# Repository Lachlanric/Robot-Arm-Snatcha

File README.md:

# "Snatcha"

4-DoF Robotic Arm (excluding end effector) + Claw Gripper.

Entire robot (minus electronics) can be laser cut from 3mm wood or acrylic and fastened with M3 screws.

Can be controlled over UART communication (requires USB to UART converter) using either:
1. IK pose control python app `Operation/IK Control/app.py`
   
   OR
2. Oculus Quest 2 controller unity app `Operation/VR Control/Unity`

https://github.com/user-attachments/assets/1d7107a9-4986-4063-b4a9-3a9e8fb0a1fe

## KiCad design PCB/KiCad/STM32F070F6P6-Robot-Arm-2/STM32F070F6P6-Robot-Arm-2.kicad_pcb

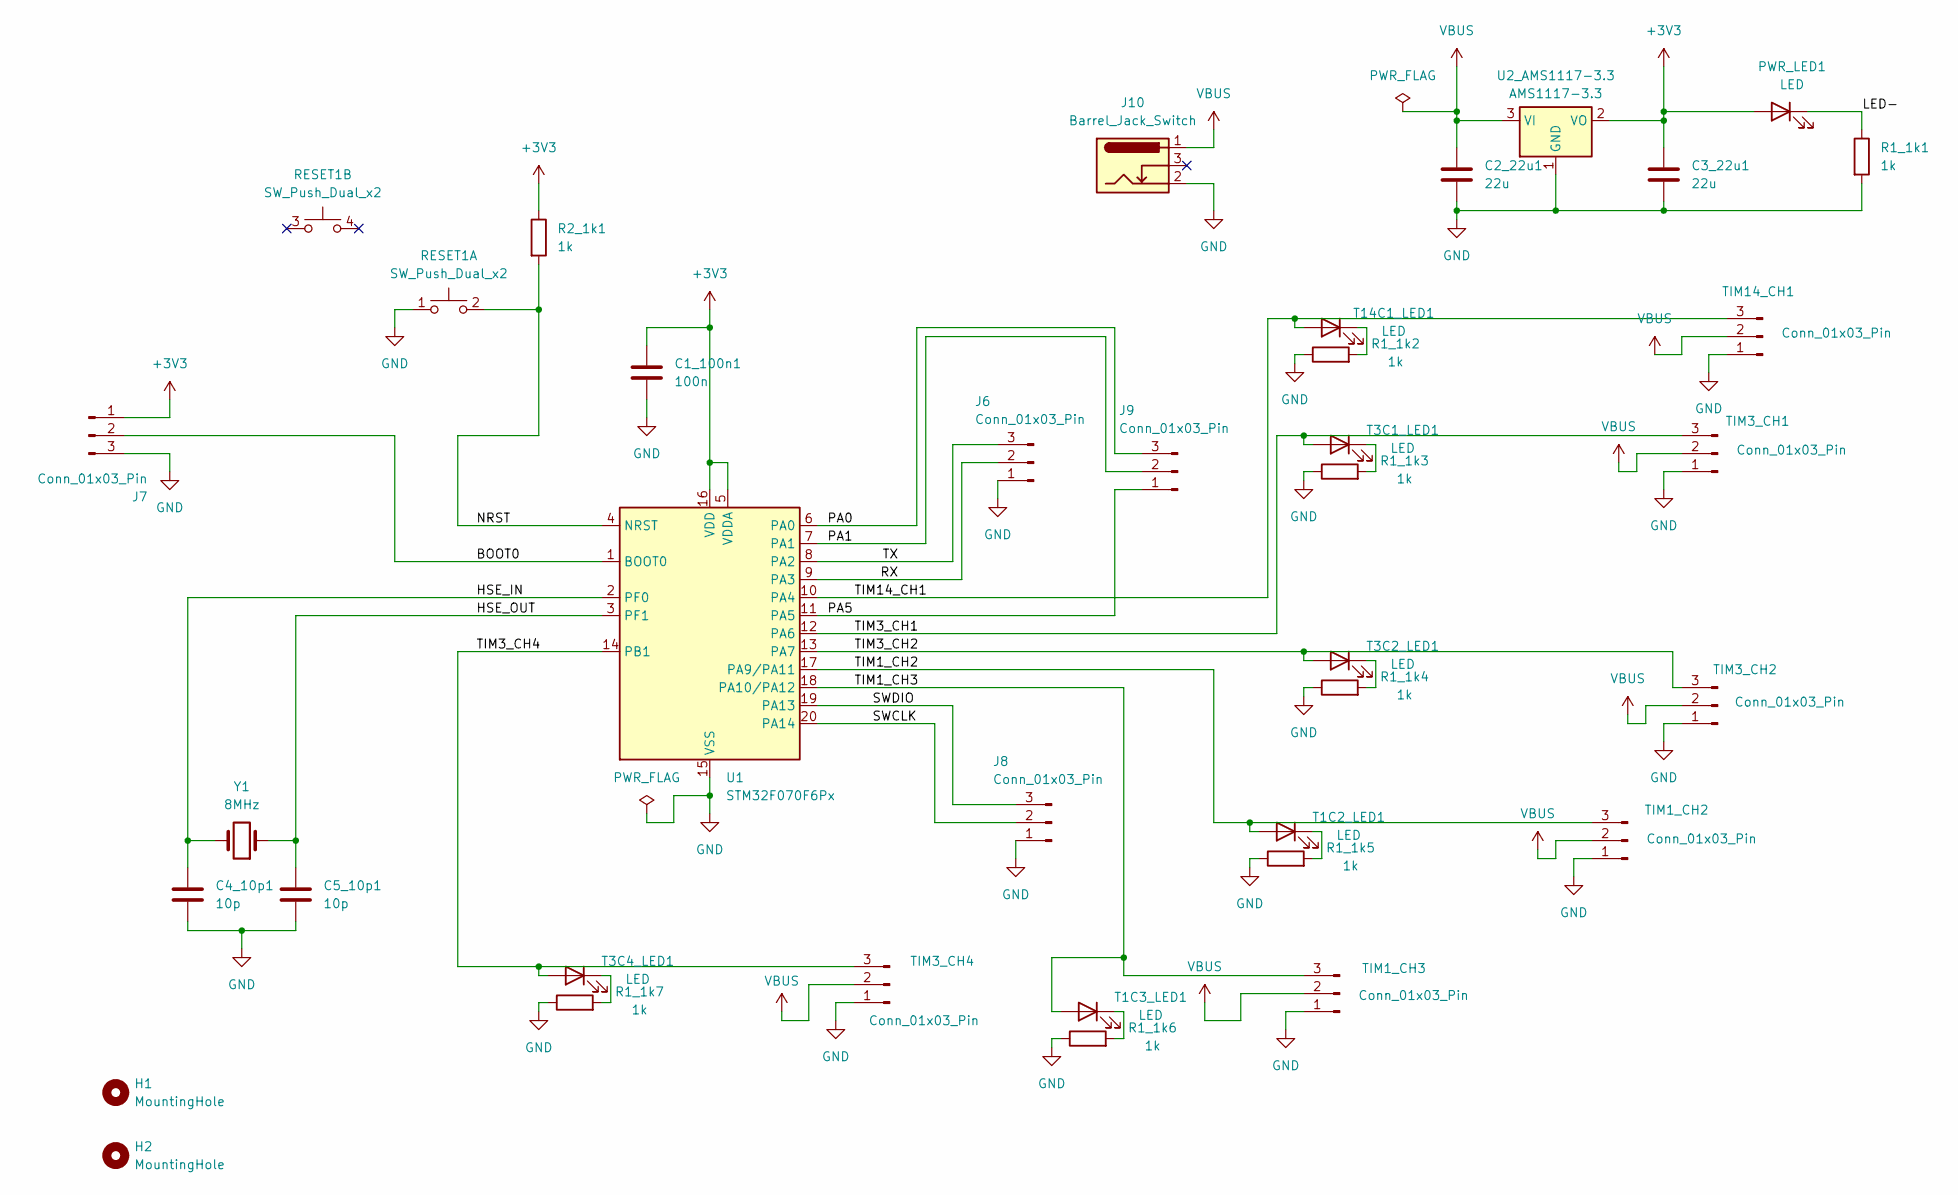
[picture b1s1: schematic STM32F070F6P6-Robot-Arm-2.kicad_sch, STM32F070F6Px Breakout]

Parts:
C1_100n1: 100n; C_1206_3216Metric_Pad1.33x1.80mm_HandSolder
C2_22u1, C3_22u1: 22u; C_1206_3216Metric_Pad1.33x1.80mm_HandSolder
C4_10p1, C5_10p1: 10p; C_Disc_D3.0mm_W1.6mm_P2.50mm
H1, H2: MountingHole; MountingHole_3.2mm_M3
J6, J7, J8, J9: Conn_01x03_Pin; PinHeader_1x03_P2.54mm_Vertical
J10: Barrel_Jack_Switch; BarrelJack_Horizontal
PWR_LED1: LED; LED_1206_3216Metric_Pad1.42x1.75mm_HandSolder
R1_1k1, R1_1k2, R1_1k3, R1_1k4, R1_1k5, R1_1k6, R1_1k7, R2_1k1: 1k; R_1206_3216Metric_Pad1.30x1.75mm_HandSolder
RESET1: SW_Push_Dual_x2; SW_PUSH_6mm
T1C2_LED1, T1C3_LED1, T3C1_LED1, T3C2_LED1, T3C4_LED1, T14C1_LED1: LED; LED_1206_3216Metric_Pad1.42x1.75mm_HandSolder
TIM1_CH2, TIM1_CH3, TIM3_CH1, TIM3_CH2, TIM3_CH4, TIM14_CH1: Conn_01x03_Pin; PinHeader_1x03_P2.54mm_Vertical
U1: STM32F070F6Px; TSSOP-20_4.4x6.5mm_P0.65mm
U2_AMS1117-3.3: AMS1117-3.3; SOT-223-3_TabPin2
Y1: 8MHz; Crystal_HC49-4H_Vertical

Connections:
+3V3: C1_100n1.1, C3_22u1.1, J7.1, PWR_LED1.2 (A), R2_1k1.1, U1.5 (VDDA), U1.16 (VDD), U2_AMS1117-3.3.2 (VO)
/BOOT0: J7.2, U1.1 (BOOT0)
/HSE_IN: C4_10p1.1, U1.2 (PF0), Y1.2
/HSE_OUT: C5_10p1.1, U1.3 (PF1), Y1.1
/LED-: PWR_LED1.1 (K), R1_1k1.1
/NRST: R2_1k1.2, RESET1.2 (D), U1.4 (NRST)
/PA0: J9.3, U1.6 (PA0)
/PA1: J9.2, U1.7 (PA1)
/PA5: J9.1, U1.11 (PA5)
/RX: J6.2, U1.9 (PA3)
/SWCLK: J8.2, U1.20 (PA14)
/SWDIO: J8.3, U1.19 (PA13)
/TIM1_CH2: T1C2_LED1.2 (A), TIM1_CH2.3, U1.17 (PA9/PA11)
/TIM1_CH3: T1C3_LED1.2 (A), TIM1_CH3.3, U1.18 (PA10/PA12)
/TIM3_CH1: T3C1_LED1.2 (A), TIM3_CH1.3, U1.12 (PA6)
/TIM3_CH2: T3C2_LED1.2 (A), TIM3_CH2.3, U1.13 (PA7)
/TIM3_CH4: T3C4_LED1.2 (A), TIM3_CH4.3, U1.14 (PB1)
/TIM14_CH1: T14C1_LED1.2 (A), TIM14_CH1.3, U1.10 (PA4)
/TX: J6.3, U1.8 (PA2)
GND: C1_100n1.2, C2_22u1.2, C3_22u1.2, C4_10p1.2, C5_10p1.2, J6.1, J7.3, J8.1, J10.2, R1_1k1.2, R1_1k2.1, R1_1k3.1, R1_1k4.1, R1_1k5.1, R1_1k6.1, R1_1k7.1, RESET1.1 (C), TIM1_CH2.1, TIM1_CH3.1, TIM3_CH1.1, TIM3_CH2.1, TIM3_CH4.1, TIM14_CH1.1, U1.15 (VSS), U2_AMS1117-3.3.1 (GND)
unnamed: R1_1k5.2, T1C2_LED1.1 (K)
unnamed: R1_1k6.2, T1C3_LED1.1 (K)
unnamed: R1_1k3.2, T3C1_LED1.1 (K)
unnamed: R1_1k4.2, T3C2_LED1.1 (K)
unnamed: R1_1k7.2, T3C4_LED1.1 (K)
unnamed: R1_1k2.2, T14C1_LED1.1 (K)
VBUS: C2_22u1.1, J10.1, TIM1_CH2.2, TIM1_CH3.2, TIM3_CH1.2, TIM3_CH2.2, TIM3_CH4.2, TIM14_CH1.2, U2_AMS1117-3.3.3 (VI)

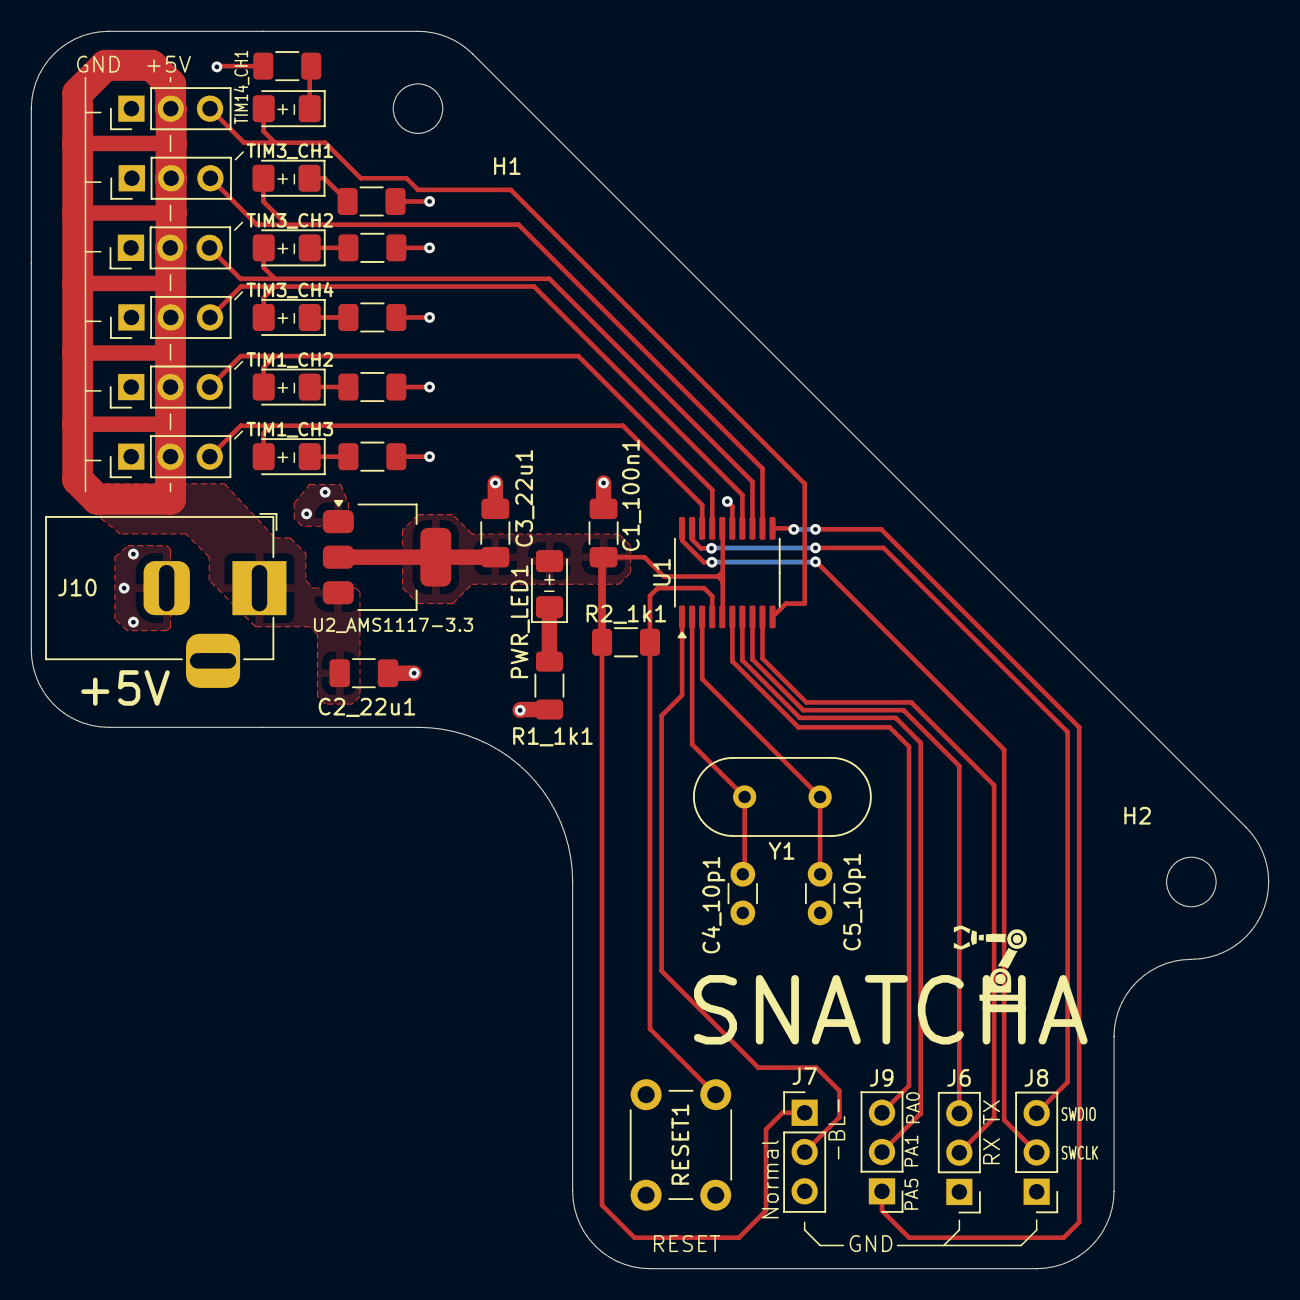
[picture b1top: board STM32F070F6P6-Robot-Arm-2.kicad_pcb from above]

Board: 2 copper layers, 80.0 x 80.0 mm, 37 parts (0 on the bottom side), 27 nets.

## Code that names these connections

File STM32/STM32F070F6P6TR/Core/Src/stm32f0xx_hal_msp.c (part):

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  /* USER CODE END TIM1_MspPostInit 0 */
    __HAL_RCC_GPIOA_CLK_ENABLE();
    /**TIM1 GPIO Configuration
    PA9     ------> TIM1_CH2
    PA10     ------> TIM1_CH3
    */
    GPIO_InitStruct.Pin = GPIO_PIN_9|GPIO_PIN_10;
    GPIO_InitStruct.Mode = GPIO_MODE_AF_PP;
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    __HAL_RCC_GPIOA_CLK_ENABLE();
    __HAL_RCC_GPIOB_CLK_ENABLE();
    /**TIM3 GPIO Configuration
    PA6     ------> TIM3_CH1
    PA7     ------> TIM3_CH2
    PB1     ------> TIM3_CH4
    */
    GPIO_InitStruct.Pin = GPIO_PIN_6|GPIO_PIN_7;
    GPIO_InitStruct.Mode = GPIO_MODE_AF_PP;
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
    __HAL_RCC_GPIOA_CLK_ENABLE();
    /**TIM14 GPIO Configuration
    PA4     ------> TIM14_CH1
    */
    GPIO_InitStruct.Pin = GPIO_PIN_4;
    GPIO_InitStruct.Mode = GPIO_MODE_AF_PP;
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
    __HAL_RCC_GPIOA_CLK_ENABLE();
    /**USART2 GPIO Configuration
    PA2     ------> USART2_TX
    PA3     ------> USART2_RX
    */
    GPIO_InitStruct.Pin = GPIO_PIN_2|GPIO_PIN_3;
    GPIO_InitStruct.Mode = GPIO_MODE_AF_PP;
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    __HAL_RCC_USART2_CLK_DISABLE();

    /**USART2 GPIO Configuration
    PA2     ------> USART2_TX
    PA3     ------> USART2_RX
    */
    HAL_GPIO_DeInit(GPIOA, GPIO_PIN_2|GPIO_PIN_3);

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
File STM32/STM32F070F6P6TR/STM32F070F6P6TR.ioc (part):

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Mcu.Name=STM32F070F6Px
Mcu.Package=TSSOP20
Mcu.UserName=STM32F070F6Px
PA1.Signal=GPIO_Output
PA10.Signal=S_TIM1_CH3
PA13.Mode=Serial_Wire
PA13.Signal=SYS_SWDIO
PA14.Mode=Serial_Wire
PA14.Signal=SYS_SWCLK
PA2.Mode=Asynchronous
PA2.Signal=USART2_TX
PA3.Mode=Asynchronous
PA3.Signal=USART2_RX
PA4.Signal=S_TIM14_CH1
PA6.Signal=S_TIM3_CH1
PA7.Signal=S_TIM3_CH2
PA9.Signal=S_TIM1_CH2
PB1.Signal=S_TIM3_CH4
PF0-OSC_IN.Mode=HSE-External-Oscillator
PF0-OSC_IN.Signal=RCC_OSC_IN
PF1-OSC_OUT.Mode=HSE-External-Oscillator
PF1-OSC_OUT.Signal=RCC_OSC_OUT
RCC.SYSCLKFreq_VALUE=48000000
RCC.SYSCLKSource=RCC_SYSCLKSOURCE_PLLCLK
board=custom

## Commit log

2025-02-05 Added files
2025-02-05 Updated READMEs and folders
2025-02-05 Added video to readme
2025-02-05 MD video
2025-02-05 Update README.md. Added video
2025-02-05 Expanded readme
2025-02-07 Added holes for motor screws. Added laser cutting files.
2025-02-07 Correction to cutting instructions
2025-02-07 backups
2025-02-07 Updated schematic
2025-02-08 Updated images

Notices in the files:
STM32/STM32F070F6P6TR/Core/Src/stm32f0xx_hal_msp.c:
Copyright (c) 2024 STMicroelectronics.
All rights reserved.
This software is licensed under terms that can be found in the LICENSE file
